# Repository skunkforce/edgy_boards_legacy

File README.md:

# Decompose all the things!
the philosophy behind this 'edgy_boards' project is to decompose electronic circuits into their basic blocks with standardized connections between them. The goal is to allow reuse of as many parts of the design as possible such that only the novel pieces require effort. In this repository you will find a growing collection of small basic circuits which can be connected together using [put_on_edge](https://github.com/skunkforce/put_on_edge) connectors.

# Design guides
There is a list of best practices reguarding the put_on_edge connectors used [here](https://github.com/skunkforce/put_on_edge/README.md). Beyond that this project has some of its own spectifications which should be followed. Boards should be made up of 16mm high x 24mm wide units subtracting 3mm space for the connectors. this means that a board which is 2 units wide and 4 units high would be 2 x 24mm = 48mm - 3mm = 45mm wide and 4 x 16mm = 64mm - 3mm = 61mm high. Most boards are 1 unit in size or 13mm x 21mm. With and height being multiples of the 8mm bump spacing of legos was intentional. 

# contributing

# contents by category
## Ethernet
### Switches 
**b034** 5 port switch using KSZ8895

**Status:** on hold untill the chips are availible.

**b035** 7 port gigabit switch using KSZ9477

**Status:** abandoned untill the chips are availible again.

**b042** 7 port gigabit switch using KSZ9897

**Status:** abandoned untill the chips are availible again.

**b098** 5 port gigabit switch with 5 (S/R/G)MII interfaces using SJA1105.

**Status:** initial.

### Connectors
**b004** 100BASE-T connector featuring a Würth 7499211121A RJ45 connector with builtin magnetics and PoE rectifier.

**Status:** tested. 

**b010** 1000BASE-T connector featuring a Würth 615008145521 RJ45 connector.

**Status:** potential problem with 009 pinning.

**b038** 1000BASE-T connector featuring Würth 7499111121A RJ45 connector.

**Status:** review needed.

**b039** gigabit SGMII cage.

**Status:** review needed.

**b086** 1000BASE-T connector featuring A70-112-331N126 PoE capable Magjack.

**Status:** ordered.

**b095** osf.009 100BASE-T M12 connector with PoE capable 749013011A magnetics.

**Status:** ordered.

### Magnetics
**b009** 1000BASE-T magnetics in phy to device configuration featuring WE7490220122.

**Status:** potential problem with 009 pinning.

**b060** 1000BASE-T magnetics in extractor/injector configuration featuring WE7490220122.

**Status:** ordered.

### Phys
**b007** 100Mbit PHY featuring LAN8742A

**Status:** tested with b004.

**b008** 100Mbit PHY featuring KSZ8081RND

**Status:** not finished.

**b037** gigabit phy using KSZ9031

**Status:** abandoned untill the chips are availible again.

**b040** gigabit phy using DP83822

**Status:** abandoned untill the chips are availible again.

**b041** gigabit phy ad RMII master using DP83822

**Status:** abandoned untill the chips are availible again.

**b054** gigabit phy using DP83848

**Status:** abandoned untill the chips are availible again.

**b078** 100Mbit MAC + PHY with SPI interface W5500

**Status:** [tested](b078_Ethernet_MAC+PHY_WIZ5500/README.md).

### Bridges
**b016** 100Mbit usb to ethernet bridge.

**Status:** ordered.

### PoE
**b011** PoE++ Rectifier using LT4321

**status:** ordered, not tested.

**b012** PoE Rectifier using MB10FTR

**status:** ordered, not tested.

**b027** PoE++ PD using LT4275

**b029** PoE++ PSE using LTC4266

**b033** PoE PD with 3 Watt flyback DCDC using MP8007 and POE30P50. 
See also **b093** for 7 Watt and **b075** for 13 Watt.

**Status:** needs improvement.

**b093** PoE PD with 7 Watt flyback DCDC using MP8007 and POE70P50. 
See also **b033** for 3 Watt and **b075** for 13 Watt.

**Status:** ordered.

**b075** PoE PD with 13 Watt flyback DCDC using MP8007 and POE13P50. 
See also **b033** for 3 Watt and **b093** for 7 Watt.

**Status:** initial.

**b052** PoE PD with buck DCDC using MP8007

**Status:** ordered.

**b076** PoE PD with flyback DCDC using SI3404

**Status:** ordered.

**b077** PoE PD buck DCDC using SI3404

**Status:** incapable of large loads, being investigated.

## USB
**b006** 4 port USB hub featuring GL850G.

**Status:** tested.

**b094** 7 port USB hub featuring USB2517.

**Status:** ordered.

**b082** 4 port USB hub featuring USB2514B.

**Status:** unfinished.

**b017** USB to debug edge using FT2232

**Status:** ordered.

**b070** USB to debug V3MODS

**Status:** ordered.

**b021** USB to I2C host using FT260S

**Status:** unfinished.

**b022** USB to I2C device using FT201XS

**Status:** ordered.

**b051** USB C connector

**Status:** tested.

## 1-wire
**b043** 1wire to I2C bridge using DS28E18

**Status:** ordered, not tested.

**b044** 1wire to SPI bridge using DS28E18

**Status:** ordered, not tested.

**b045** 1wire to RJ45 connector

**Status:** review needed.

**b048** I2C 1wire master DS2484R

**Status:** review needed.

## CAN
**b087** CAN controller with SPI interface featuring MCP2515

**status** initial design.

### FD
**b065** CAN FD controller with SPI interface featuring MCP2517FD

**status** ordered.

**b066** CAN FD transceiver featuring TJA1441

**status** ordered.

## Regulator
### Switching
**b063** Isolated 5v-5v DCDC.

**Status:** ordered.

**b069** 4.5V to 75V input 5A buck DCDC MIC28515.

**Status:** ordered.

**b068** 6.5V to 28V input 5A buck DCDC AOZ2152EQI-28.

**Status:** ordered.

**b025** USB to 4x DCDC 

**Status:** tested.

**b057** 4.5V to 75V buck converter MAX17760
Output current 300ma

**Status:** needs review.

**b085** 4.2V - 18V input 2A buck converter AP6220

**Status:** ordered.

### LDO
**b002** features a TCR2EF33 producing 3.3V output from a 5 volt input. 
Output current 200ma.

**Status:** tested

## Microcontroller
**b018** breakout of the RP2040 including flash memory.

**Status:** [b018v2.2rc missing I2C resistors, basic functionality otherwise tested](https://github.com/skunkforce/things_on_edge/releases/tag/b018v2.2rc)

[b018v2.3rc ready to order](https://github.com/skunkforce/things_on_edge/releases/tag/b018v2.3rc)

**b019** breakout of the STM32F042.

**Status:** finished but not ordered (or tested) because STM32F042 is out of stock.

**b080** breakout of the STM32G030.

**Status:** ordered.

**b023** breakout of the STM23F723IE

**Status:** outdated and probably dorment untill the chips are availible again.

**b026** breakout of STM32F7 144 pin TQFP

**Status:** outdated and probably dorment untill the chips are availible again.

**b030** breakout of STM32F7 100 pin TQFP

**Status:** outdated and probably dorment untill the chips are availible again.

**b032** breakout of STM32F7 100 pin TFBGA

**Status:** outdated and probably dorment untill the chips are availible again.

**b028** STM32F042 with just one I2C connector.

**Status:** abandoned.

**b020** STM32F745 breakout.

**Status:** abandoned untill the chip is availible again.

**b053** STM32F107 64TQFP breakout.

**Status:** abandoned untill the chip is availible again.

**b090** STM32WL55 LoRa breakout.

**Status:** initial.

## system on a module
### standard SOM connector layout
It is common for boards which connect to a SOM to connect to multiple interfaces. Therefore it is advantagous to standardize the interface connector layout of SOMs such that connecting boards can connect at multiple points. 

Using the standard 16mm distance between connectors the order of connected interfaces is:
USB
UART
I2C
SPI
DebugEdge

**b049** Raspberry Pi compute module 4 with isolated flyback PoE. 

**Status:** this board is essentially a composition of b076, b080 and a CM4. development of this is paused untill those are fully tested.

**b071** Raspberry Pi compute module 4. 

**Status:** waiting for tests of b049.

## Pinconnectors
**b003** generic jumper pins on a pass through connector.

**b005** generic pin sockets on a pass through connector.

**b014** ADC to SMA

**status:** tested. 

## ADC
**b013** ADS868x

**status:** ordered, not tested.

**b031** ADS8688 8X differential SPI ADC

**status:** tested.

**b059** ADS8168 8X differential SPI ADC 1MSPS

**status:** review needed.

**b056** ADS131M08 8X differential SPI ADC 32kSPS

**status:** ordered.

**b081** MCP3428 4X 16 bit differential I2C ADC with PGA 15SPS

**status:** ordered.

**b084** ADS131M03 3X differential SPI ADC 32kSPS

**status:** ordered.

**b091** ADS131A04 4X differential SPI ADC 128kSPS

**status:** initial.

## DAC
**b024** 4x DAC with I2C interface using MCP4728.

**Status:** ordered, not tested.

## Isolators
**b036** I2C isolator featuring ADUM1251

**Status:** ordered, not yet tested.

**b055** SPI isolator and DCDC featuring ADUM5411

**Status:** unfinished.

**b064** SPI isolator and DCDC featuring ADUM5401

**Status:** unfinished.

**b062** SPI isolator featuring MAX14483

**Status:** unfinished.

## Memory
**b046** I2C eeprom M24C02

**Status:** test needed.

**b079** SPI SD card

**Status:** ordered.

**b073** QSPI EEPROM

**Status:** ordered.

**b072** QSPI EEPROM W25Q

**Status:** ordered.

**b096** MAC address chip 11AA02E48 or 11AA02E64

**Status:** initial.

## Sensors
### angle

**b089** 3 axis accelerometer LIS3DHTR.

**Status:** initial.

### hall effect

**b015** MLX91205.

**status:** not finished.

**b047** HDC1080.

**status:** review needed.

**b092** TMCS110.

**status:** initial.

### temperature

**b083** 4x PT100 to I2C using MCP3428.

**status:** ordered.

**b088** temp humid SHT30-DIS.

**status:** initial.

## Analog
**b050** analog preamp using LMV601

**Status:** review needed.

## Other
**b058** RTC MCP79410

**Status:** review needed.

**b061** 40 pin pi 4 connector breakout

**Status:** tested.

**b097** GPIO to RGB-LED

**Status:** initial.

**b074** resistive power supply tester

**Status:** initial.

unused b067

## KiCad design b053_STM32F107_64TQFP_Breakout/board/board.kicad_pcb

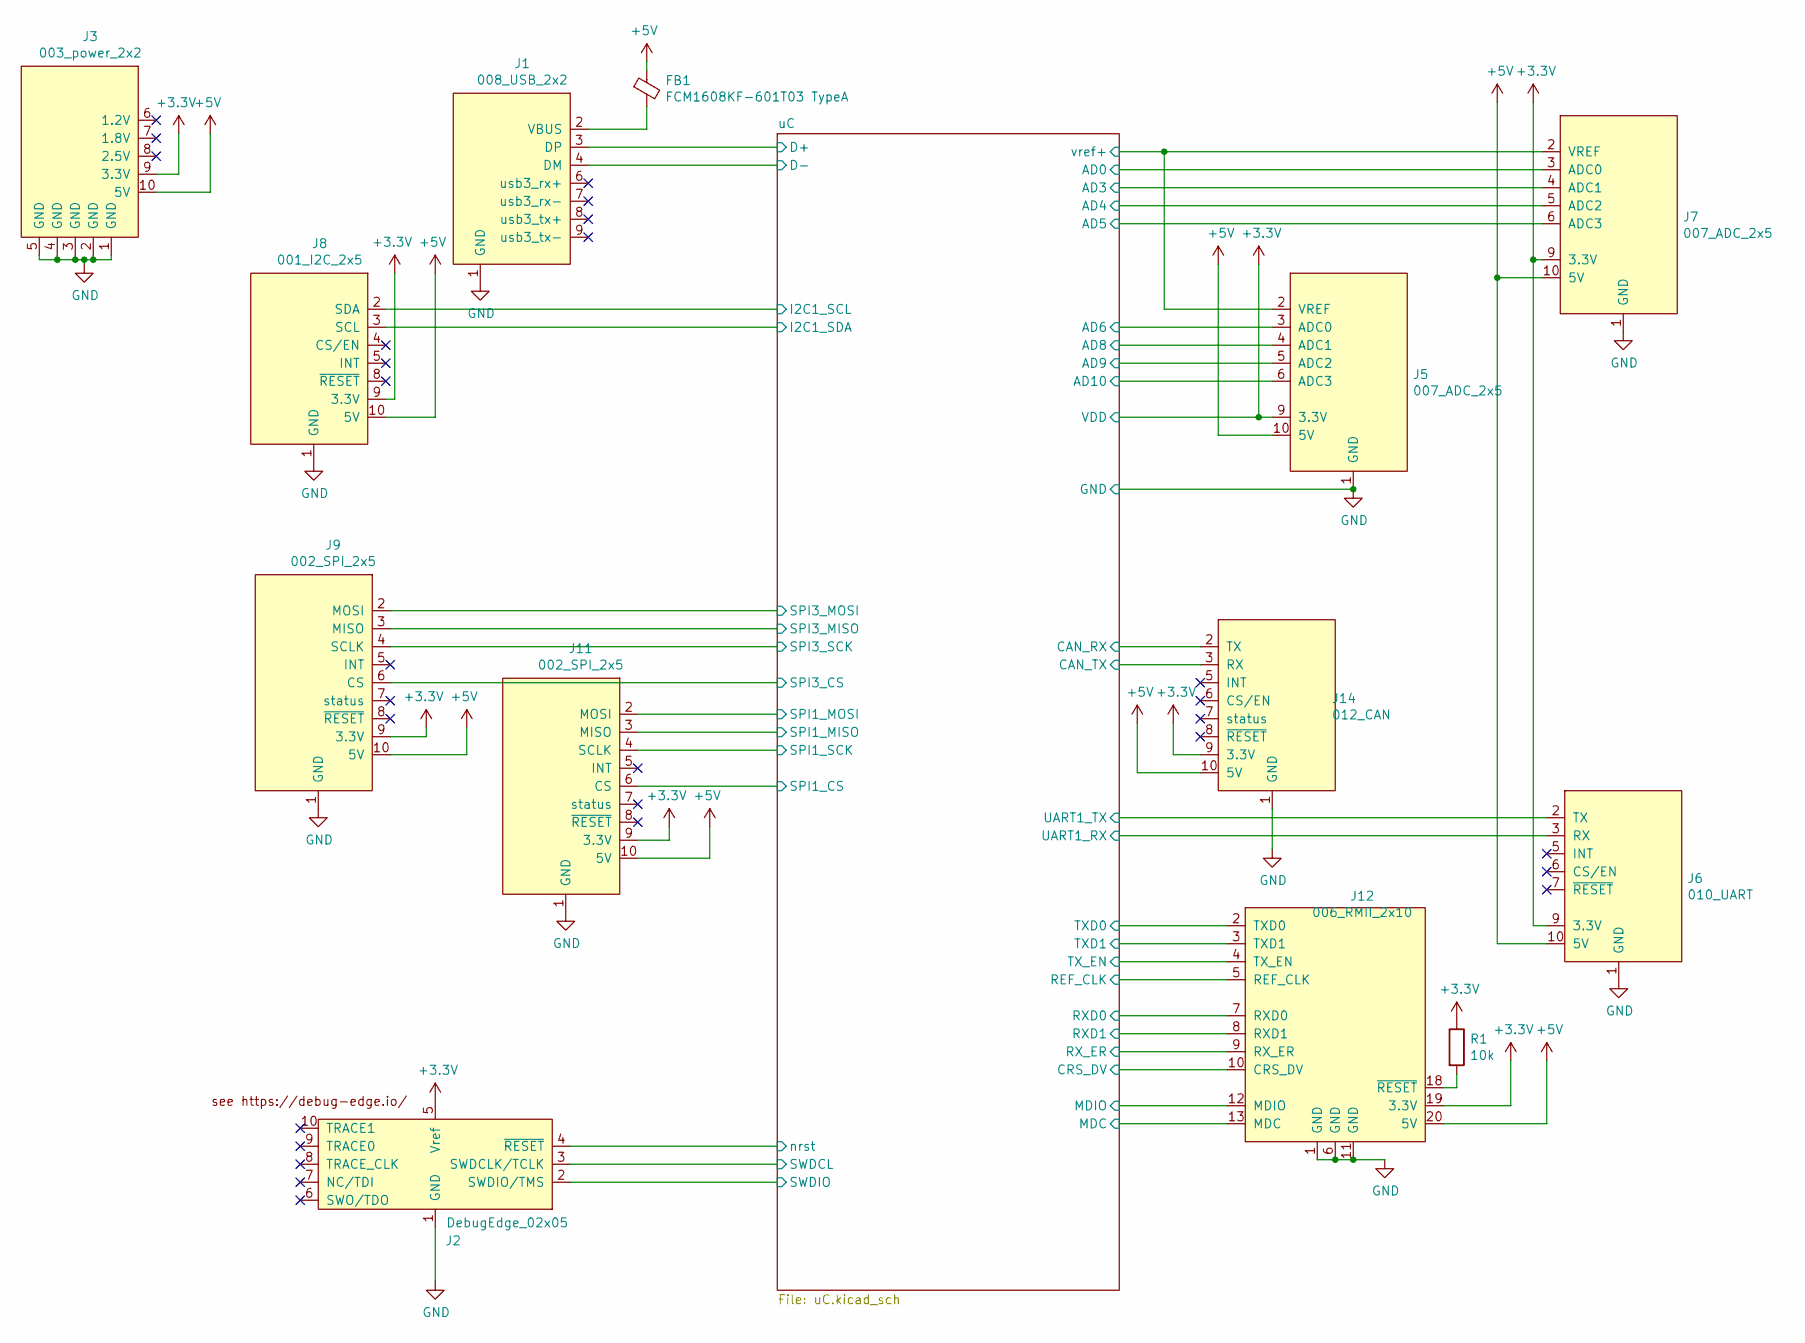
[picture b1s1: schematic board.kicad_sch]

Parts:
FB1: FCM1608KF-601T03 TypeA; L_0805_2012Metric
J1: 008_USB_2x2; on_edge_2x05_device
J2: DebugEdge_02x05; on_edge_2x05_device
J3: 003_power_2x2; on_edge_2x05_device
J5, J7: 007_ADC_2x5; on_edge_2x05_host
J6: 010_UART; on_edge_2x05_up_host
J8: 001_I2C_2x5; on_edge_2x05_up_host
J9, J11: 002_SPI_2x5; on_edge_2x05_up_host
J12: 006_RMII_2x10; on_edge_2x10_host
J14: 012_CAN; on_edge_2x05_up_host
R1: 10k; R_0603_1608Metric_Pad1.05x0.95mm_HandSolder

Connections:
+3V3: J2.5 (Vref), J3.9 (3.3V), J5.9 (3.3V), J6.9 (3.3V), J7.9 (3.3V), J8.9 (3.3V), J9.9 (3.3V), J11.9 (3.3V), J12.19 (3.3V), J14.9 (3.3V), R1.1; also elsewhere on the board
+5V: FB1.1, J3.10 (5V), J5.10 (5V), J6.10 (5V), J7.10 (5V), J8.10 (5V), J9.10 (5V), J11.10 (5V), J12.20 (5V), J14.10 (5V)
/uC/AD0: J7.3 (ADC0); also elsewhere on the board
/uC/AD3: J7.4 (ADC1); also elsewhere on the board
/uC/AD4: J7.5 (ADC2); also elsewhere on the board
/uC/AD5: J7.6 (ADC3); also elsewhere on the board
/uC/AD6: J5.3 (ADC0); also elsewhere on the board
/uC/AD8: J5.4 (ADC1); also elsewhere on the board
/uC/AD9: J5.5 (ADC2); also elsewhere on the board
/uC/AD10: J5.6 (ADC3); also elsewhere on the board
/uC/CAN_RX: J14.2 (TX); also elsewhere on the board
/uC/CAN_TX: J14.3 (RX); also elsewhere on the board
/uC/CRS_DV: J12.10 (CRS_DV); also elsewhere on the board
/uC/D+: J1.3 (DP); also elsewhere on the board
/uC/D-: J1.4 (DM); also elsewhere on the board
/uC/I2C1_SCL: J8.2 (SDA); also elsewhere on the board
/uC/I2C1_SDA: J8.3 (SCL); also elsewhere on the board
/uC/MDC: J12.13 (MDC); also elsewhere on the board
/uC/MDIO: J12.12 (MDIO); also elsewhere on the board
/uC/REF_CLK: J12.5 (REF_CLK); also elsewhere on the board
/uC/RXD0: J12.7 (RXD0); also elsewhere on the board
/uC/RXD1: J12.8 (RXD1); also elsewhere on the board
/uC/RX_ER: J12.9 (RX_ER); also elsewhere on the board
/uC/SPI1_CS: J11.6 (CS); also elsewhere on the board
/uC/SPI1_MISO: J11.3 (MISO); also elsewhere on the board
/uC/SPI1_MOSI: J11.2 (MOSI); also elsewhere on the board
/uC/SPI1_SCK: J11.4 (SCLK); also elsewhere on the board
/uC/SPI3_CS: J9.6 (CS); also elsewhere on the board
/uC/SPI3_MISO: J9.3 (MISO); also elsewhere on the board
/uC/SPI3_MOSI: J9.2 (MOSI); also elsewhere on the board
/uC/SPI3_SCK: J9.4 (SCLK); also elsewhere on the board
/uC/SWDCL: J2.3 (SWDCLK/TCLK); also elsewhere on the board
/uC/SWDIO: J2.2 (SWDIO/TMS); also elsewhere on the board
/uC/TXD0: J12.2 (TXD0); also elsewhere on the board
/uC/TXD1: J12.3 (TXD1); also elsewhere on the board
/uC/TX_EN: J12.4 (TX_EN); also elsewhere on the board
/uC/UART1_RX: J6.3 (RX); also elsewhere on the board
/uC/UART1_TX: J6.2 (TX); also elsewhere on the board
/uC/nrst: J2.4 (~RESET); also elsewhere on the board
/vref+: J5.2 (VREF), J7.2 (VREF)
GND: J1.1 (GND), J2.1 (GND), J3.1 (GND), J3.2 (GND), J3.3 (GND), J3.4 (GND), J3.5 (GND), J5.1 (GND), J6.1 (GND), J7.1 (GND), J8.1 (GND), J9.1 (GND), J11.1 (GND), J12.1 (GND), J12.6 (GND), J12.11 (GND), J14.1 (GND); also elsewhere on the board
unnamed: FB1.2, J1.2 (VBUS)
unnamed: J12.18 (~RESET), R1.2

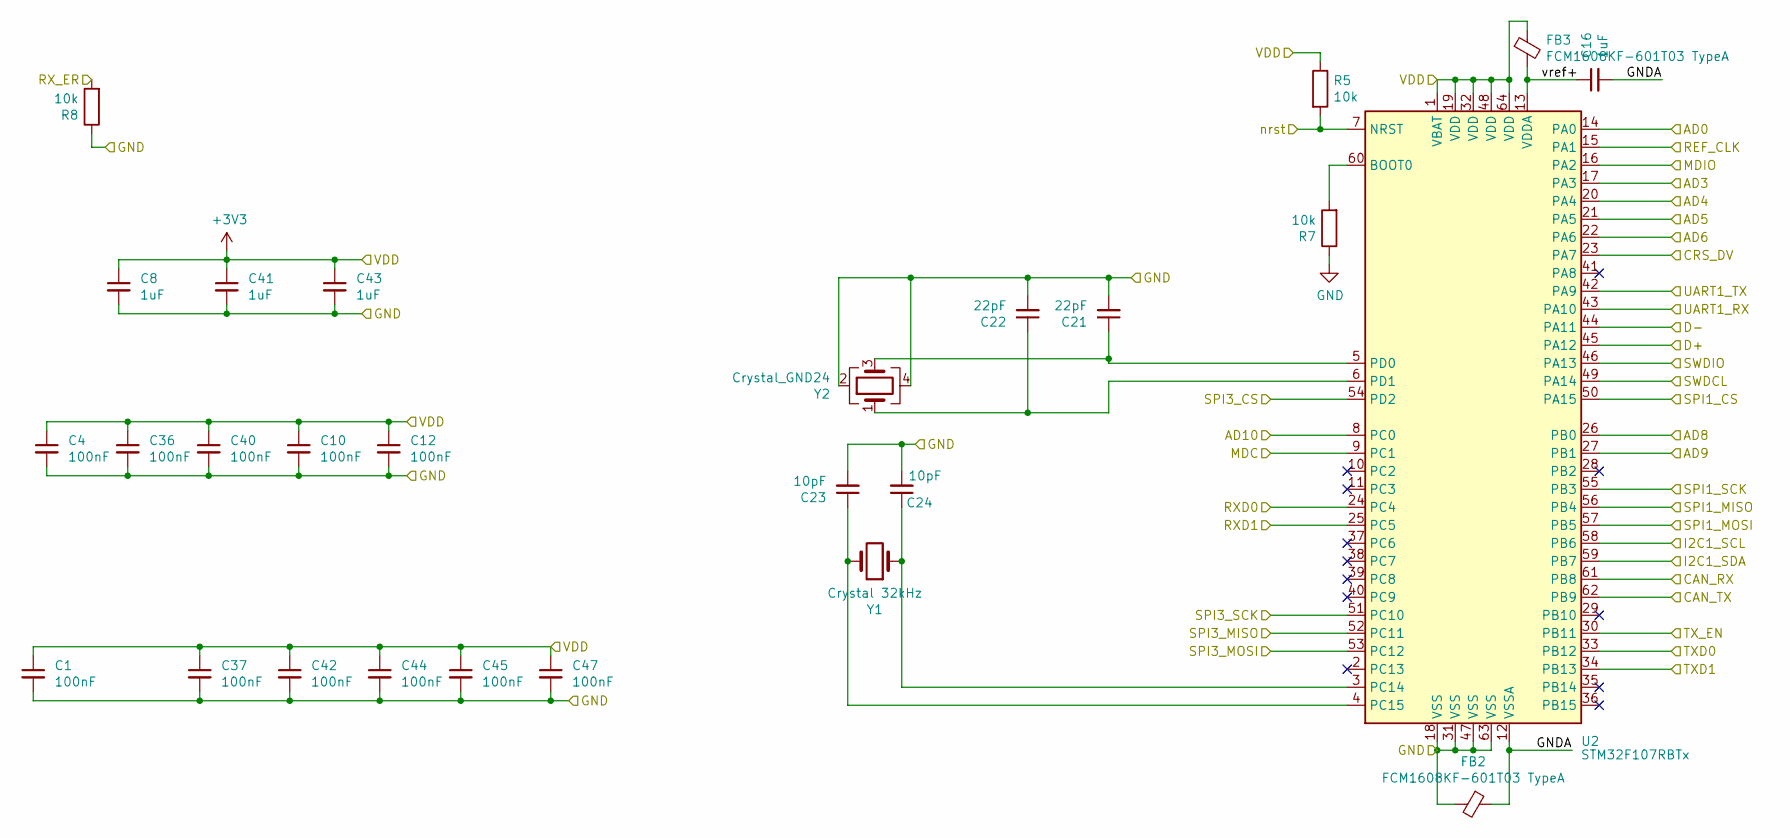
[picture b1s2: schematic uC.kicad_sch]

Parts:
C1, C4, C10, C12, C36, C37, C40, C42, C44, C45, C47: 100nF; C_0603_1608Metric
C8, C16, C41, C43: 1uF; C_0603_1608Metric
C21, C22: 22pF; C_0603_1608Metric_Pad1.05x0.95mm_HandSolder
C23, C24: 10pF; C_0603_1608Metric_Pad1.05x0.95mm_HandSolder
FB2, FB3: FCM1608KF-601T03 TypeA; L_0805_2012Metric
R5, R7, R8: 10k; R_0603_1608Metric_Pad1.05x0.95mm_HandSolder
U2: STM32F107RBTx; LQFP-64_10x10mm_P0.5mm
Y1: Crystal 32kHz; Crystal_SMD_3215-2Pin_3.2x1.5mm; Digi-Key_PN 644-1156-1-ND
Y2: Crystal_GND24; Crystal_SMD_Abracon_ABM8G-4Pin_3.2x2.5mm; Digi-Key_PN 535-9140-1-ND

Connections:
+3V3: C1.1, C4.1, C8.1, C10.1, C12.1, C36.1, C37.1, C40.1, C41.1, C42.1, C43.1, C44.1, C45.1, C47.1, FB3.1, R5.1, U2.1 (VBAT), U2.19 (VDD), U2.32 (VDD), U2.48 (VDD), U2.64 (VDD); also elsewhere on the board
/uC/AD0: U2.14 (PA0); also elsewhere on the board
/uC/AD3: U2.17 (PA3); also elsewhere on the board
/uC/AD4: U2.20 (PA4); also elsewhere on the board
/uC/AD5: U2.21 (PA5); also elsewhere on the board
/uC/AD6: U2.22 (PA6); also elsewhere on the board
/uC/AD8: U2.26 (PB0); also elsewhere on the board
/uC/AD9: U2.27 (PB1); also elsewhere on the board
/uC/AD10: U2.8 (PC0); also elsewhere on the board
/uC/CAN_RX: U2.61 (PB8); also elsewhere on the board
/uC/CAN_TX: U2.62 (PB9); also elsewhere on the board
/uC/CRS_DV: U2.23 (PA7); also elsewhere on the board
/uC/D+: U2.45 (PA12); also elsewhere on the board
/uC/D-: U2.44 (PA11); also elsewhere on the board
/uC/GNDA: C16.2, FB2.1, U2.12 (VSSA)
/uC/I2C1_SCL: U2.58 (PB6); also elsewhere on the board
/uC/I2C1_SDA: U2.59 (PB7); also elsewhere on the board
/uC/MDC: U2.9 (PC1); also elsewhere on the board
/uC/MDIO: U2.16 (PA2); also elsewhere on the board
/uC/REF_CLK: U2.15 (PA1); also elsewhere on the board
/uC/RXD0: U2.24 (PC4); also elsewhere on the board
/uC/RXD1: U2.25 (PC5); also elsewhere on the board
/uC/RX_ER: R8.2; also elsewhere on the board
/uC/SPI1_CS: U2.50 (PA15); also elsewhere on the board
/uC/SPI1_MISO: U2.56 (PB4); also elsewhere on the board
/uC/SPI1_MOSI: U2.57 (PB5); also elsewhere on the board
/uC/SPI1_SCK: U2.55 (PB3); also elsewhere on the board
/uC/SPI3_CS: U2.54 (PD2); also elsewhere on the board
/uC/SPI3_MISO: U2.52 (PC11); also elsewhere on the board
/uC/SPI3_MOSI: U2.53 (PC12); also elsewhere on the board
/uC/SPI3_SCK: U2.51 (PC10); also elsewhere on the board
/uC/SWDCL: U2.49 (PA14); also elsewhere on the board
/uC/SWDIO: U2.46 (PA13); also elsewhere on the board
/uC/TXD0: U2.33 (PB12); also elsewhere on the board
/uC/TXD1: U2.34 (PB13); also elsewhere on the board
/uC/TX_EN: U2.30 (PB11); also elsewhere on the board
/uC/UART1_RX: U2.43 (PA10); also elsewhere on the board
/uC/UART1_TX: U2.42 (PA9); also elsewhere on the board
/uC/nrst: R5.2, U2.7 (NRST); also elsewhere on the board
/uC/vref+: C16.1, FB3.2, U2.13 (VDDA)
GND: C1.2, C4.2, C8.2, C10.2, C12.2, C21.2, C22.2, C23.2, C24.2, C36.2, C37.2, C40.2, C41.2, C42.2, C43.2, C44.2, C45.2, C47.2, FB2.2, R7.1, R8.1, U2.18 (VSS), U2.31 (VSS), U2.47 (VSS), U2.63 (VSS), Y2.2, Y2.4; also elsewhere on the board
unnamed: C21.1, U2.5 (PD0), Y2.3
unnamed: C22.1, U2.6 (PD1), Y2.1
unnamed: C23.1, U2.4 (PC15), Y1.2
unnamed: C24.1, U2.3 (PC14), Y1.1
unnamed: R7.2, U2.60 (BOOT0)

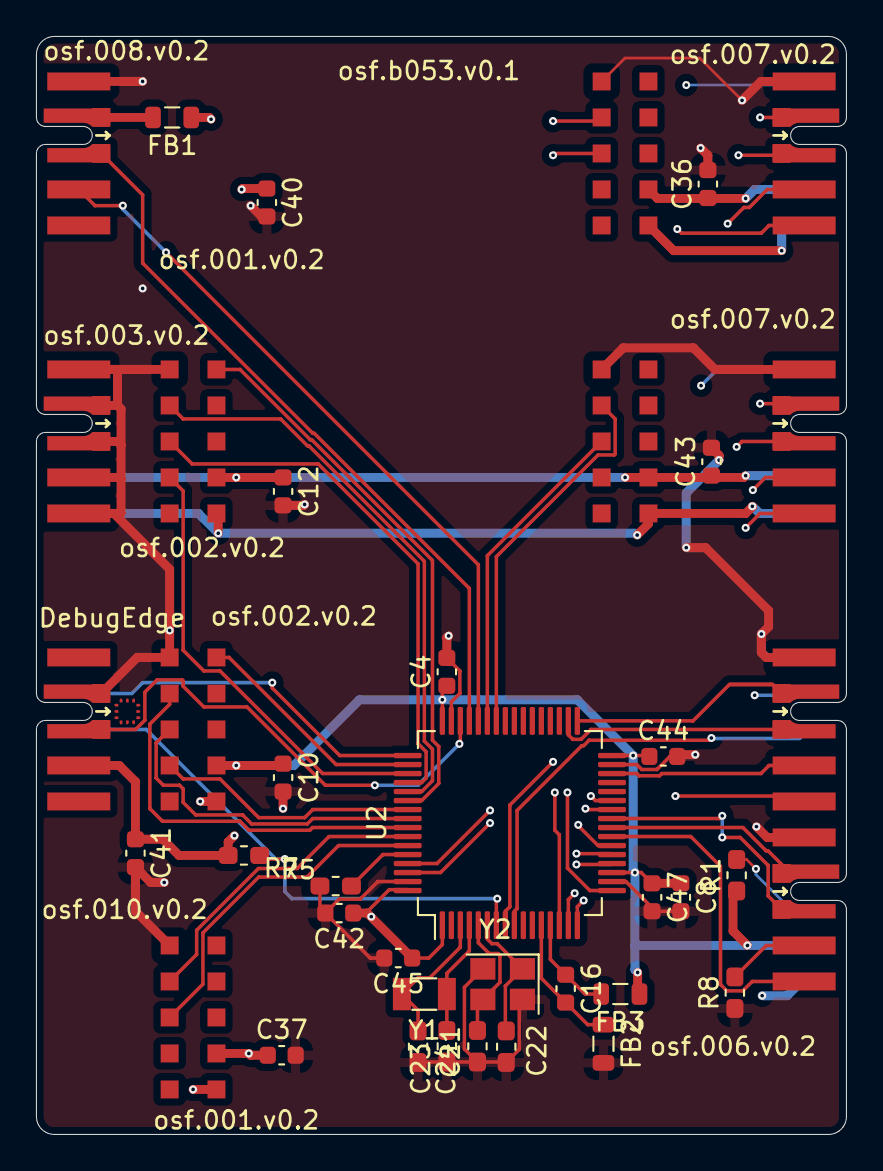
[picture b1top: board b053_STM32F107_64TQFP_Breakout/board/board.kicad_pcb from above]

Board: 4 copper layers, 45.0 x 61.0 mm, 40 parts (1 on the bottom side), 50 nets.

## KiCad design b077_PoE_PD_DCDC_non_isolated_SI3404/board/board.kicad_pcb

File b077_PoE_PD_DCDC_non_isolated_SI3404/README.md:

# b077 PoE PD DCDC non isolated

# tests
The b077v0.1 board was connected to the center taps connector of a b078v0.1 board connected to a PoE switch (Netgear GS108PP). 5v was measured with an oscilliscope on the output with 5ma load. There was roughly 20mv of rippele on the output of 5.4V. This is as expected.
There were some issues discussed in pull request #67 which were resolved with wire. The next version will most likely be a release. 

# alternative components
If the full 3A are not needed one can substitute some of the components for cheaper ones. 

for 1.5A:
D3 SL210A-TP
L1 NRS8040T470MJGK

for 630ma
D3 SL210A-TP
L1 NRS5024T330MMGJ

for 100ma
D3 BAT46W
L1 MLZ2012M470WT000

for lesser loads one should be able to use smaller input and output caps.

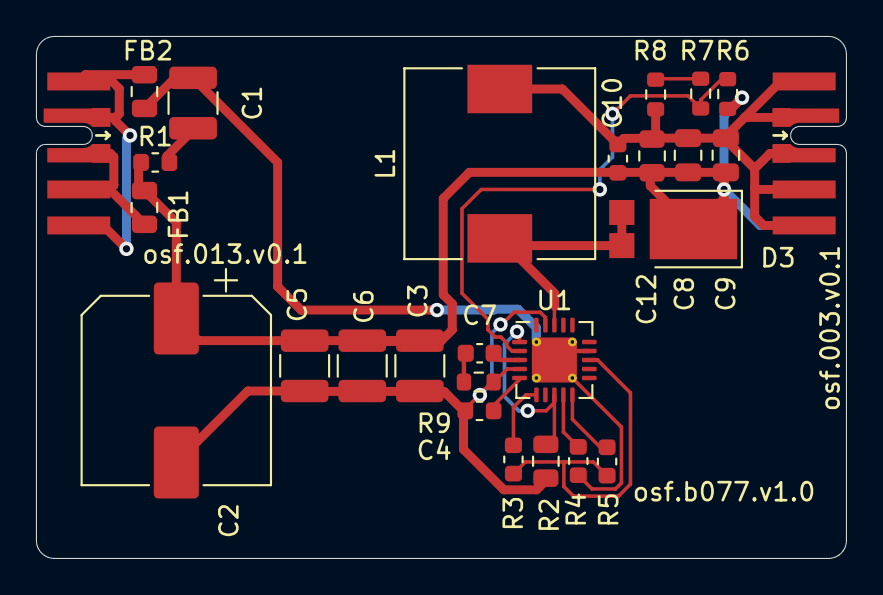
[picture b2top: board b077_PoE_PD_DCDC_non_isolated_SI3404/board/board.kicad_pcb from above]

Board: 2 copper layers, 45.0 x 29.0 mm, 27 parts (0 on the bottom side), 18 nets.

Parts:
C1, C5: 100nF; C_1210_3225Metric
C2: 10uF; CP_Elec_10x10
C3: 1uF; C_1210_3225Metric
C4: 100nF; C_0603_1608Metric
C6: 10nF; C_1210_3225Metric
C7: 330pF; C_0603_1608Metric
C8, C9, C12: 100uF; C_0805_2012Metric
C10: 1uF; C_0603_1608Metric
D3: PDS3100; D_PowerDI-5
FB1, FB2: 700R; L_0805_2012Metric
J1: 013_PoE_rectified; on_edge_2x05_device
J2: 003_power; on_edge_2x05_host
L1: 47uH; L_10.4x10.4_H4.8
R1: 3R; R_0603_1608Metric
R2: 1.2R; R_0805_2012Metric
R3: 24.3k; R_0603_1608Metric
R4: 75R; R_0603_1608Metric
R5: 88.7k; R_0603_1608Metric
R6: 3.24k; R_0603_1608Metric
R7: 9.09k; R_0603_1608Metric
R8: 10R; R_0603_1608Metric
R9: 143k; R_0603_1608Metric
U1: Si3404; QFN-20-1EP_4x4mm_P0.5mm_EP2.5x2.5mm_ThermalVias

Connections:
/dcdc/5V: C2.1, C3.1, C5.1, C6.1, C8.1, C9.1, C10.1, C12.1, D3.1 (K), FB1.2, J2.10 (5V), R1.1, R6.1
/dcdc/48V: FB1.1, J1.3 (48V), J1.4 (48V)
/dcdc/FBH: R6.2, R7.1, U1.2 (FBH)
/dcdc/GND2: C8.2, C9.2, C10.2, C12.2, J2.1 (GND), J2.2 (GND), J2.3 (GND), J2.4 (GND), J2.5 (GND), L1.2, R8.2
/dcdc/erout: C7.1, U1.3 (EROUT)
GND: FB2.1, J1.1 (GND), J1.2 (GND), J1.5 (GND)
unnamed: C1.1, R1.2
unnamed: C1.2, FB2.2, R4.1, U1.14 (VNEG), U1.21 (EPAD)
unnamed: C7.2, R9.1
unnamed: D3.2 (A), L1.1, U1.18 (SWO)
unnamed: R2.2, U1.1 (ISNS), U1.8 (HSO)
unnamed: R3.1, U1.6 (RDET)
unnamed: R3.2, R5.2, U1.13 (VPOS)
unnamed: R4.2, U1.9 (RCL)
unnamed: R5.1, U1.10 (RFREQ)
unnamed: R7.2, R8.1
VDD: C4.2, U1.5 (VDD)
VSS: C2.2, C3.2, C4.1, C5.2, C6.2, R2.1, R9.2, U1.4 (FBL), U1.19 (VSS)

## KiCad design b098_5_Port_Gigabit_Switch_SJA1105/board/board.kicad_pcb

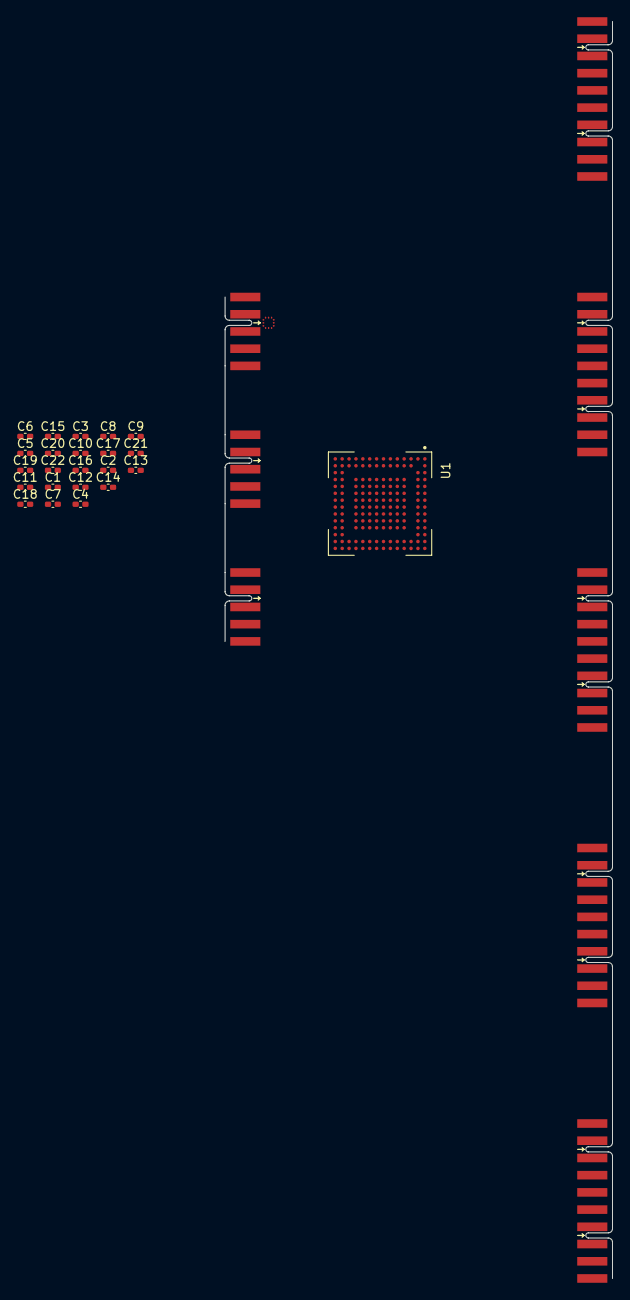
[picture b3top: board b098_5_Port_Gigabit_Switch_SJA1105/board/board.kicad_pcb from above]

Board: 2 copper layers, 31 parts (0 on the bottom side), 94 nets, no tracks yet.

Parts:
C1, C5, C6, C7, C8, C9, C10, C11, C12, C15, C16, C17, C18, C19, C20, C21, C22: 100nF; C_0402_1005Metric_Pad0.74x0.62mm_HandSolder
C2, C3, C4, C13, C14: 1uF; C_0402_1005Metric_Pad0.74x0.62mm_HandSolder
J1: DebugEdge_02x05; debug_edge_2x05_device
J2: 002_SPI; on_edge_2x05_device
J3, J4, J5, J6, J7: 015_RGMII; on_edge_2x10_host
J8: 003_power; on_edge_2x05_device
U1: SJA1105ELY; BGA159C80P14X14_1200X1200X150N

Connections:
/switch/MII0_RXC: J3.11 (RXC), U1.E2 (MII0_RX_CLK/RXC)
/switch/MII0_RXD0: J3.12 (RXD0), U1.E1 (MII0_RXD0)
/switch/MII0_RXD1: J3.13 (RXD1), U1.F2 (MII0_RXD1)
/switch/MII0_RXD2: J3.14 (RXD2), U1.F1 (MII0_RXD2)
/switch/MII0_RXD3: J3.15 (RXD3), U1.G2 (MII0_RXD3)
/switch/MII0_RX_CTL: J3.16 (RX_CTL), U1.G1 (MII0_RX_DV/CRS_DV/RX_CTL)
/switch/MII0_RX_ER: J3.10 (RXER), U1.H2 (MII0_RX_ER)
/switch/MII0_TXC: J3.2 (TXC), U1.D1 (MII0_TX_CLK/REF_CLK/TXC)
/switch/MII0_TXD0: J3.3 (TXD0), U1.A2 (MII0_TXD0)
/switch/MII0_TXD1: J3.4 (TXD1), U1.B1 (MII0_TXD1)
/switch/MII0_TXD2: J3.5 (TXD2), U1.C2 (MII0_TXD2)
/switch/MII0_TXD3: J3.6 (TXD3), U1.C1 (MII0_TXD3)
/switch/MII0_TX_CTL: J3.7 (TX_CTL), U1.D2 (MII0_TX_EN/TX_CTL)
/switch/MII0_TX_ER: J3.9 (TXER), U1.A3 (MII0_TX_ER)
/switch/MII1_RXC: J4.11 (RXC), U1.B6 (MII1_RX_CLK/RXC)
/switch/MII1_RXD0: J4.12 (RXD0), U1.A6 (MII1_RXD0)
/switch/MII1_RXD1: J4.13 (RXD1), U1.B5 (MII1_RXD1)
/switch/MII1_RXD2: J4.14 (RXD2), U1.A5 (MII1_RXD2)
/switch/MII1_RXD3: J4.15 (RXD3), U1.B4 (MII1_RXD3)
/switch/MII1_RX_CTL: J4.16 (RX_CTL), U1.A4 (MII1_RX_DV/CRS_DV/RX_CTL)
/switch/MII1_RX_ER: J4.10 (RXER), U1.B3 (MII1_RX_ER)
/switch/MII1_TXC: J4.2 (TXC), U1.A7 (MII1_TX_CLK/REF_CLK/TXC)
/switch/MII1_TXD0: J4.3 (TXD0), U1.B9 (MII1_TXD0)
/switch/MII1_TXD1: J4.4 (TXD1), U1.A9 (MII1_TXD1)
/switch/MII1_TXD2: J4.5 (TXD2), U1.B8 (MII1_TXD2)
/switch/MII1_TXD3: J4.6 (TXD3), U1.A8 (MII1_TXD3)
/switch/MII1_TX_CTL: J4.7 (TX_CTL), U1.B7 (MII1_TX_EN/TX_CTL)
/switch/MII1_TX_ER: J4.9 (TXER), U1.A10 (MII1_TX_ER)
/switch/MII2_RXC: J5.11 (RXC), U1.B14 (MII2_RX_CLK/RXC)
/switch/MII2_RXD0: J5.12 (RXD0), U1.A13 (MII2_RXD0)
/switch/MII2_RXD1: J5.13 (RXD1), U1.B12 (MII2_RXD1)
/switch/MII2_RXD2: J5.14 (RXD2), U1.A12 (MII2_RXD2)
/switch/MII2_RXD3: J5.15 (RXD3), U1.B11 (MII2_RXD3)
/switch/MII2_RX_CTL: J5.16 (RX_CTL), U1.A11 (MII2_RX_DV/CRS_DV/RX_CTL)
/switch/MII2_RX_ER: J5.10 (RXER), U1.B10 (MII2_RX_ER)
/switch/MII2_TXC: J5.2 (TXC), U1.C14 (MII2_TX_CLK/REF_CLK/TXC)
/switch/MII2_TXD0: J5.3 (TXD0), U1.E13 (MII2_TXD0)
/switch/MII2_TXD1: J5.4 (TXD1), U1.E14 (MII2_TXD1)
/switch/MII2_TXD2: J5.5 (TXD2), U1.D13 (MII2_TXD2)
/switch/MII2_TXD3: J5.6 (TXD3), U1.D14 (MII2_TXD3)
/switch/MII2_TX_CTL: J5.7 (TX_CTL), U1.C13 (MII2_TX_EN/TX_CTL)
/switch/MII2_TX_ER: J5.9 (TXER), U1.F14 (MII2_TX_ER)
/switch/MII3_RXC: J6.11 (RXC), U1.J13 (MII3_RX_CLK/RXC)
/switch/MII3_RXD0: J6.12 (RXD0), U1.J14 (MII3_RXD0)
/switch/MII3_RXD1: J6.13 (RXD1), U1.H13 (MII3_RXD1)
/switch/MII3_RXD2: J6.14 (RXD2), U1.H14 (MII3_RXD2)
/switch/MII3_RXD3: J6.15 (RXD3), U1.G13 (MII3_RXD3)
/switch/MII3_RX_CTL: J6.16 (RX_CTL), U1.G14 (MII3_RX_DV/CRS_DV/RX_CTL)
/switch/MII3_RX_ER: J6.10 (RXER), U1.F13 (MII3_RX_ER)
/switch/MII3_TXC: J6.2 (TXC), U1.K14 (MII3_TX_CLK/REF_CLK/TXC)
/switch/MII3_TXD0: J6.3 (TXD0), U1.M13 (MII3_TXD0)
/switch/MII3_TXD1: J6.4 (TXD1), U1.M14 (MII3_TXD1)
/switch/MII3_TXD2: J6.5 (TXD2), U1.L13 (MII3_TXD2)
/switch/MII3_TXD3: J6.6 (TXD3), U1.L14 (MII3_TXD3)
/switch/MII3_TX_CTL: J6.7 (TX_CTL), U1.K13 (MII3_TX_EN/TX_CTL)
/switch/MII3_TX_ER: J6.9 (TXER), U1.N14 (MII3_TX_ER)
/switch/MII4_RXC: J7.11 (RXC), U1.P10 (MII4_RX_CLK/RXC)
/switch/MII4_RXD0: J7.12 (RXD0), U1.N10 (MII4_RXD0)
/switch/MII4_RXD1: J7.13 (RXD1), U1.P11 (MII4_RXD1)
/switch/MII4_RXD2: J7.14 (RXD2), U1.N11 (MII4_RXD2)
/switch/MII4_RXD3: J7.15 (RXD3), U1.P12 (MII4_RXD3)
/switch/MII4_RX_CTL: J7.16 (RX_CTL), U1.N12 (MII4_RX_DV/CRS_DV/RX_CTL)
/switch/MII4_RX_ER: J7.10 (RXER), U1.P13 (MII4_RX_ER)
/switch/MII4_TXC: J7.2 (TXC), U1.N9 (MII4_TX_CLK/REF_CLK/TXC)
/switch/MII4_TXD0: J7.3 (TXD0), U1.P7 (MII4_TXD0)
/switch/MII4_TXD1: J7.4 (TXD1), U1.N7 (MII4_TXD1)
/switch/MII4_TXD2: J7.5 (TXD2), U1.P8 (MII4_TXD2)
/switch/MII4_TXD3: J7.6 (TXD3), U1.N8 (MII4_TXD3)
/switch/MII4_TX_CTL: J7.7 (TX_CTL), U1.P9 (MII4_TX_EN/TX_CTL)
/switch/MII4_TX_ER: J7.9 (TXER), U1.P6 (MII4_TX_ER)
/switch/SCK: J2.4 (SCLK), U1.P5 (SCK)
/switch/SDI: J2.2 (MOSI), U1.N5 (SDI)
/switch/SDO: J2.3 (MISO), U1.P4 (SDO)
/switch/SS_N: J2.6 (CS), U1.N6 (SS_N)
/switch/TCK: J1.3 (SWDCLK/TCLK), U1.N1 (TCK)
/switch/TDI: J1.7 (NC/TDI), U1.M2 (TDI)
/switch/TDO: J1.6 (SWO/TDO), U1.N3 (TDO)
/switch/TMS: J1.2 (SWDIO/TMS), U1.P2 (TMS)
/switch/TRST_N: J1.4 (~RESET), U1.M1 (TRST_N)
/switch/VCC_1.2V: C1.1, C10.1, C21.1
/switch/VCC_3.3V: C9.1, C20.1
/switch/VDDIO_MII0: U1.D4 (VDDIO_MII0), U1.E4 (VDDIO_MII0), U1.G4 (VDDIO_MII0)
/switch/VDDIO_MII1: U1.D5 (VDDIO_MII1), U1.D7 (VDDIO_MII1), U1.D8 (VDDIO_MII1)
/switch/VDDIO_MII2: U1.D10 (VDDIO_MII2), U1.D11 (VDDIO_MII2), U1.E11 (VDDIO_MII2)
/switch/VDDIO_MII3: U1.G11 (VDDIO_MII3), U1.H11 (VDDIO_MII3), U1.K11 (VDDIO_MII3)
/switch/VDDIO_MII4: U1.L8 (VDDIO_MII4), U1.L10 (VDDIO_MII4), U1.L11 (VDDIO_MII4)
GND: C1.2, C2.2, C3.2, C4.2, C5.2, C6.2, C7.2, C8.2, C9.2, C10.2, C11.2, C12.2, C13.2, C14.2, C15.2, C16.2, C17.2, C18.2, C19.2, C20.2, C21.2, C22.2, J1.1 (GND), J2.1 (GND), J3.1 (GND), J3.8 (GND), J3.17 (GND), J4.1 (GND), J4.8 (GND), J4.17 (GND), J5.1 (GND), J5.8 (GND), J5.17 (GND), J6.1 (GND), J6.8 (GND), J6.17 (GND), J7.1 (GND), J7.8 (GND), J7.17 (GND), J8.1 (GND), J8.2 (GND), J8.3 (GND), J8.4 (GND), J8.5 (GND), U1.A1 (VSS), U1.A14 (VSS), U1.B13 (VSS), U1.E5 (VSS), U1.E6 (VSS), U1.E7 (VSS), U1.E8 (VSS), U1.E9 (VSS), U1.E10 (VSS), U1.F5 (VSS), U1.F6 (VSS), U1.F7 (VSS), U1.F8 (VSS), U1.F9 (VSS), U1.F10 (VSS), U1.G5 (VSS), U1.G6 (VSS), U1.G7 (VSS), U1.G8 (VSS), U1.G9 (VSS), U1.G10 (VSS), U1.H5 (VSS), U1.H6 (VSS), U1.H7 (VSS), U1.H8 (VSS), U1.H9 (VSS), U1.H10 (VSS), U1.J2 (VSSA_PLL), U1.J5 (VSS), U1.J6 (VSS), U1.J7 (VSS), U1.J8 (VSS), U1.J9 (VSS), U1.J10 (VSS), U1.K4 (VSS), U1.K5 (VSS), U1.K6 (VSS), U1.K7 (VSS), U1.K8 (VSS), U1.K9 (VSS), U1.K10 (VSS), U1.L2 (VSSA_OSC), U1.L7 (VSS), U1.N2 (VSS), U1.N13 (VSS), U1.P1 (VSS), U1.P14 (VSS)
unnamed: C2.1, C5.1, U1.L5 (VDDIO_HOST)
unnamed: C4.1, C7.1, U1.K1 (VDDA_OSC)
unnamed: C3.1, C6.1, C8.1, C11.1, C12.1, C15.1, C18.1, C19.1, C22.1, U1.D6 (VDD_CORE), U1.D9 (VDD_CORE), U1.F4 (VDD_CORE), U1.F11 (VDD_CORE), U1.J4 (VDD_CORE), U1.J11 (VDD_CORE), U1.L6 (VDD_CORE), U1.L9 (VDD_CORE)
unnamed: C13.1, C16.1, U1.H4 (VDDIO_CLO)
unnamed: C14.1, C17.1, U1.J1 (VDDA_PLL)
unnamed: J3.19 (3.3V), J4.19 (3.3V), J5.19 (3.3V), J6.19 (3.3V), J7.19 (3.3V)
unnamed: J3.20 (5V), J4.20 (5V), J5.20 (5V), J6.20 (5V), J7.20 (5V)

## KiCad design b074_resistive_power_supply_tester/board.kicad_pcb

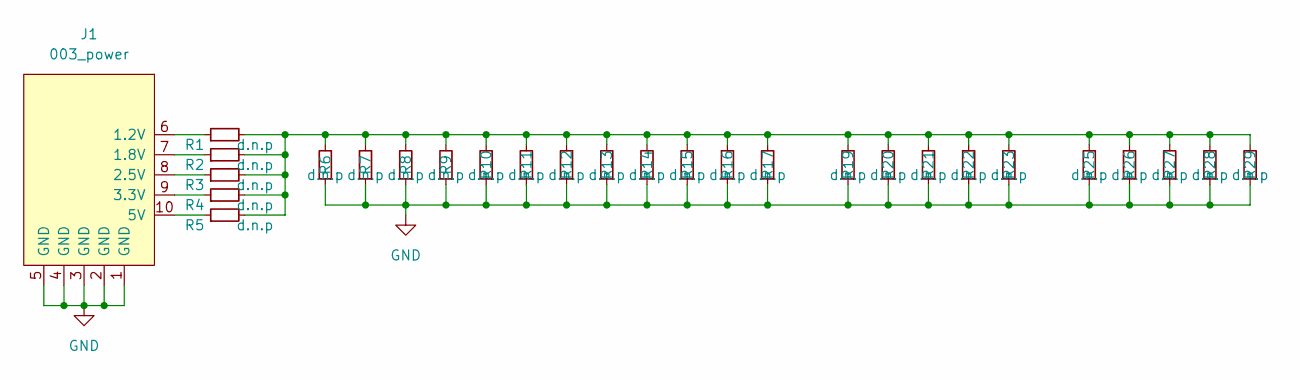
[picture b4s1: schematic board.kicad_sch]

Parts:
J1: 003_power; on_edge_2x05_device
R1, R2, R3, R4, R5: d.n.p; R_0603_1608Metric
R6, R7, R8, R9, R10, R11, R12, R13, R14, R15, R16, R17, R19, R20, R21, R22, R23, R25, R26, R27, R28, R29: d.n.p; R_1210_3225Metric

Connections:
GND: J1.1 (GND), J1.2 (GND), J1.3 (GND), J1.4 (GND), J1.5 (GND), R6.1, R7.1, R8.1, R9.1, R10.1, R11.1, R12.1, R13.1, R14.1, R15.1, R16.1, R17.1, R19.1, R20.1, R21.1, R22.1, R23.1, R25.1, R26.1, R27.1, R28.1, R29.1
unnamed: J1.6 (1.2V), R1.1
unnamed: J1.7 (1.8V), R2.1
unnamed: J1.8 (2.5V), R3.1
unnamed: J1.9 (3.3V), R4.1
unnamed: J1.10 (5V), R5.1
unnamed: R1.2, R2.2, R3.2, R4.2, R5.2, R6.2, R7.2, R8.2, R9.2, R10.2, R11.2, R12.2, R13.2, R14.2, R15.2, R16.2, R17.2, R19.2, R20.2, R21.2, R22.2, R23.2, R25.2, R26.2, R27.2, R28.2, R29.2

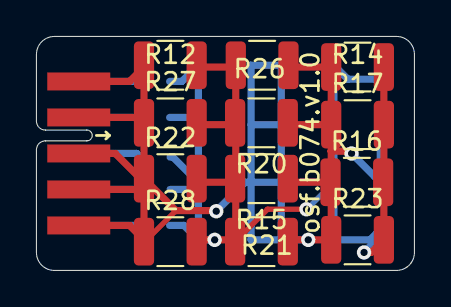
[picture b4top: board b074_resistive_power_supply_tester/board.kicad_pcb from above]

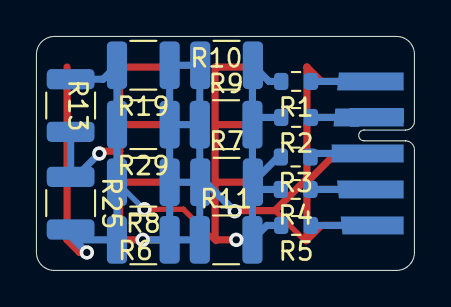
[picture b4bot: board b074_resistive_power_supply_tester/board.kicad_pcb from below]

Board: 2 copper layers, 21.0 x 13.0 mm, 28 parts (15 on the bottom side), 7 nets.

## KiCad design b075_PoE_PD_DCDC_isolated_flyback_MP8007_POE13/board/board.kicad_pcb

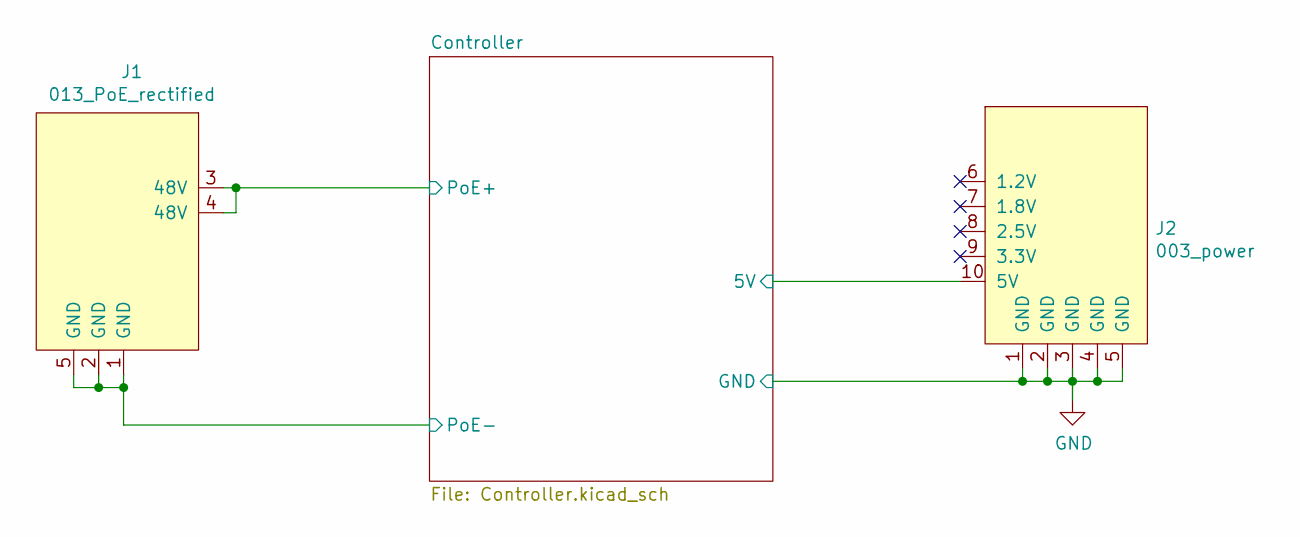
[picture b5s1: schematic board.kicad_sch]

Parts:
J1: 013_PoE_rectified; on_edge_2x05_device
J2: 003_power; on_edge_2x05_host

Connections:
/Controller/5V: J2.10 (5V); also elsewhere on the board
/Controller/PoE+: J1.3 (48V), J1.4 (48V); also elsewhere on the board
/Controller/PoE-: J1.1 (GND), J1.2 (GND), J1.5 (GND); also elsewhere on the board
GND: J2.1 (GND), J2.2 (GND), J2.3 (GND), J2.4 (GND), J2.5 (GND); also elsewhere on the board
